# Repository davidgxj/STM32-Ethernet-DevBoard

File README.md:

STM32-Ethernet-DevBoard
=======================

STM32 F4 Ethernet Board

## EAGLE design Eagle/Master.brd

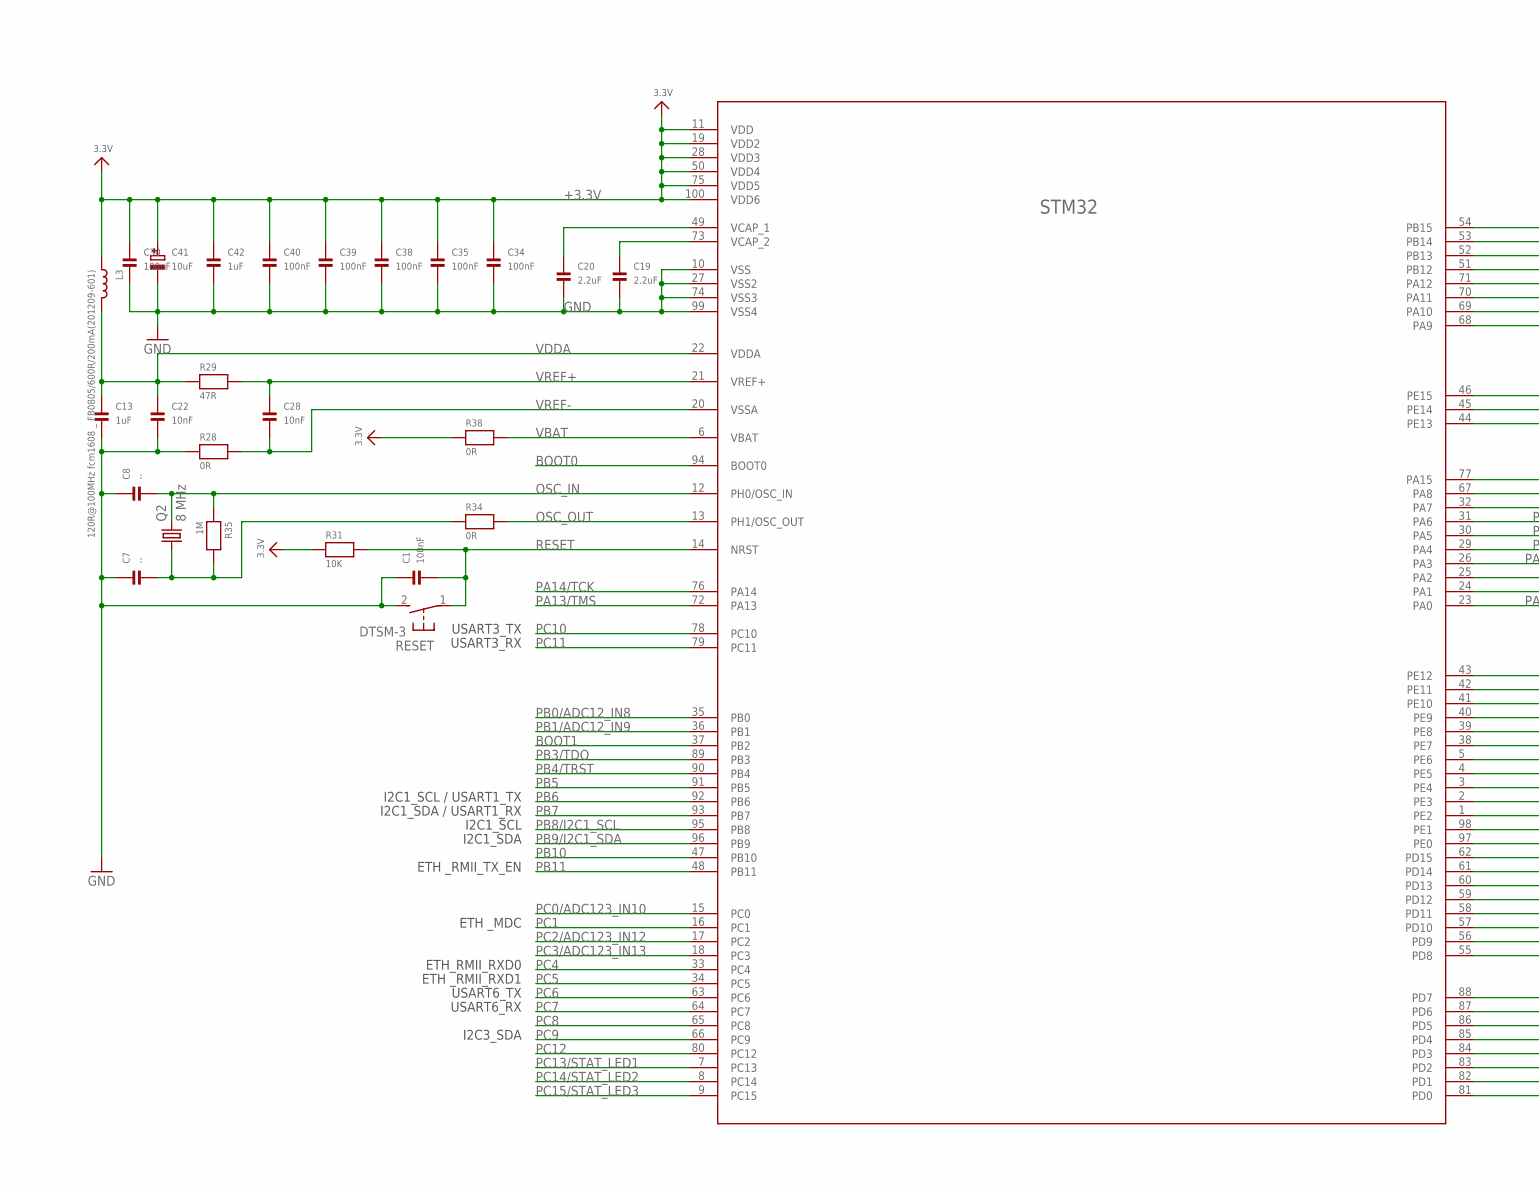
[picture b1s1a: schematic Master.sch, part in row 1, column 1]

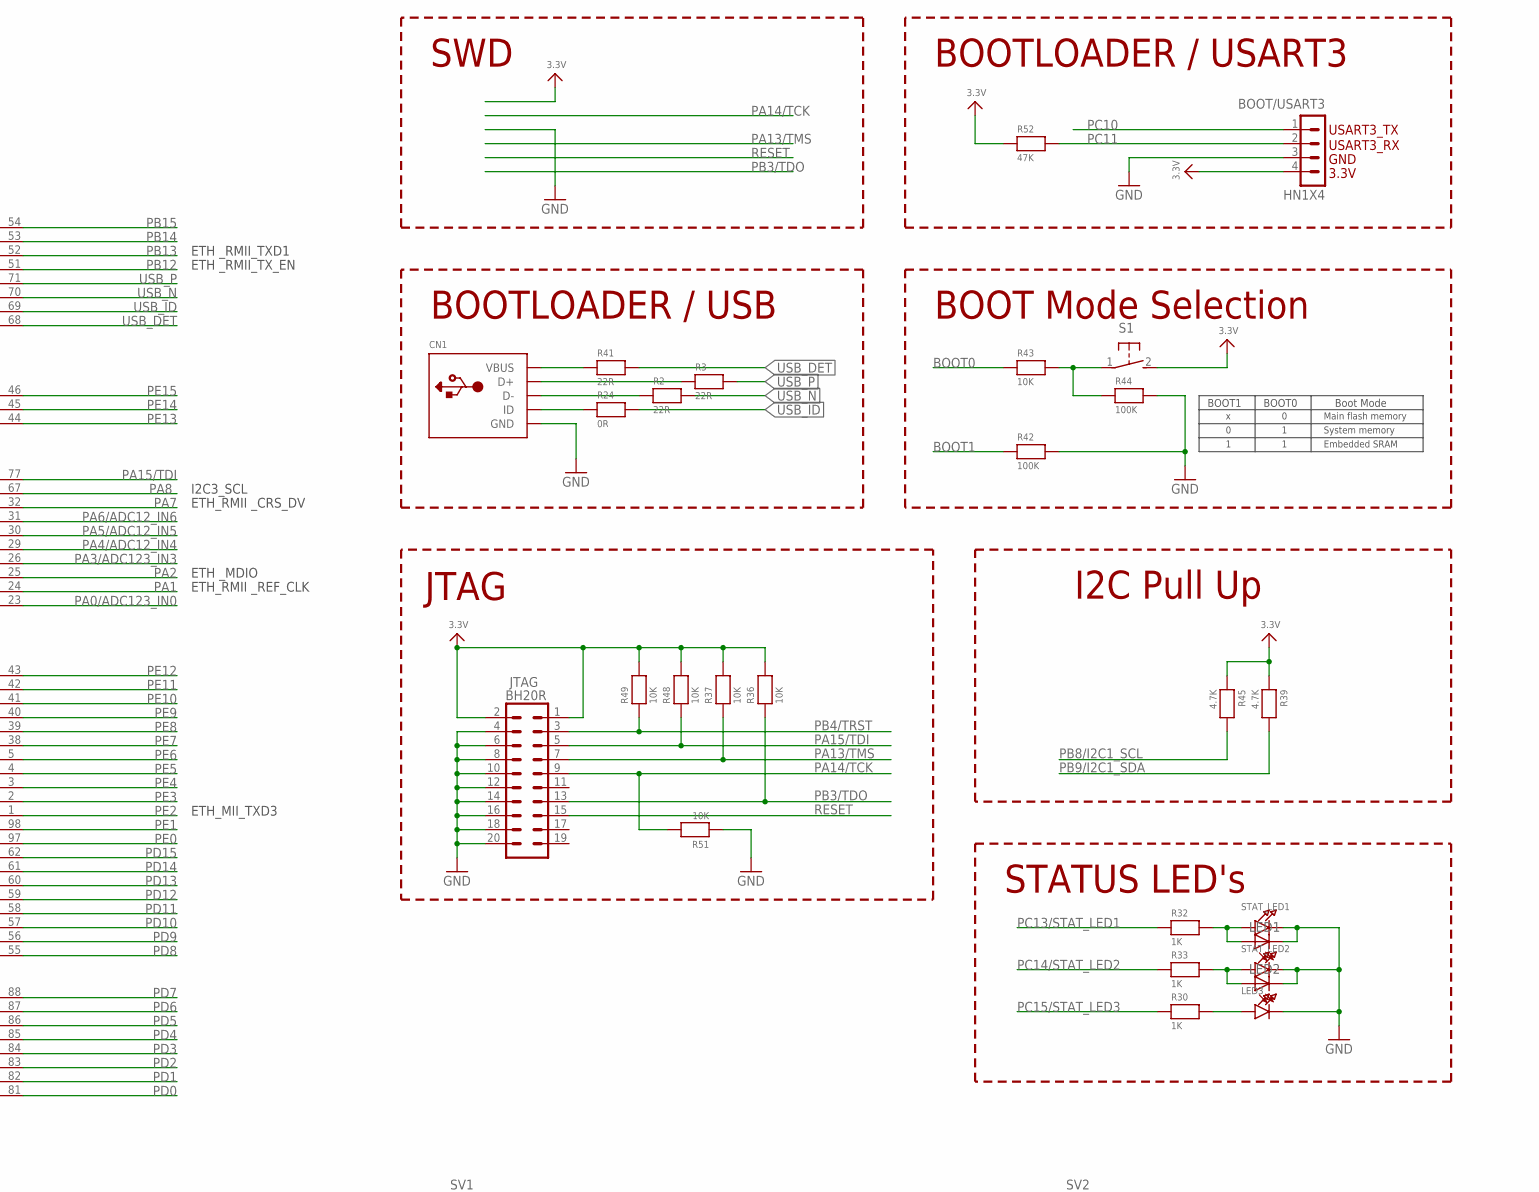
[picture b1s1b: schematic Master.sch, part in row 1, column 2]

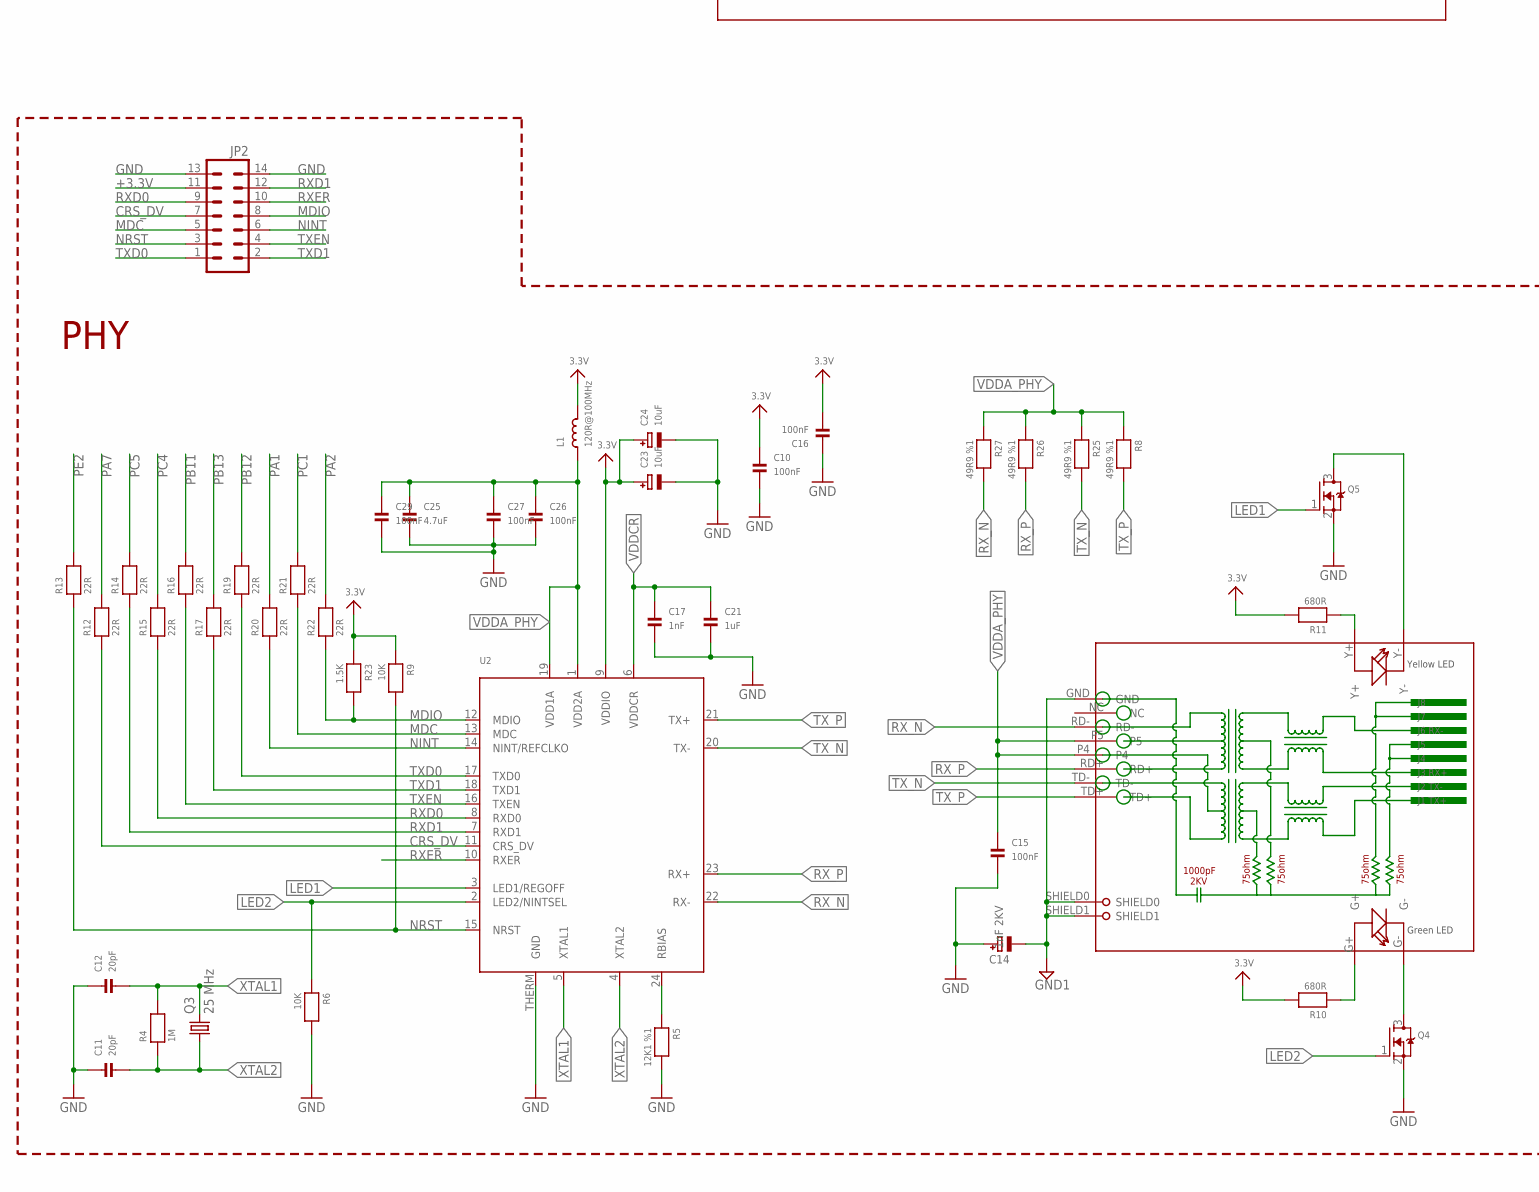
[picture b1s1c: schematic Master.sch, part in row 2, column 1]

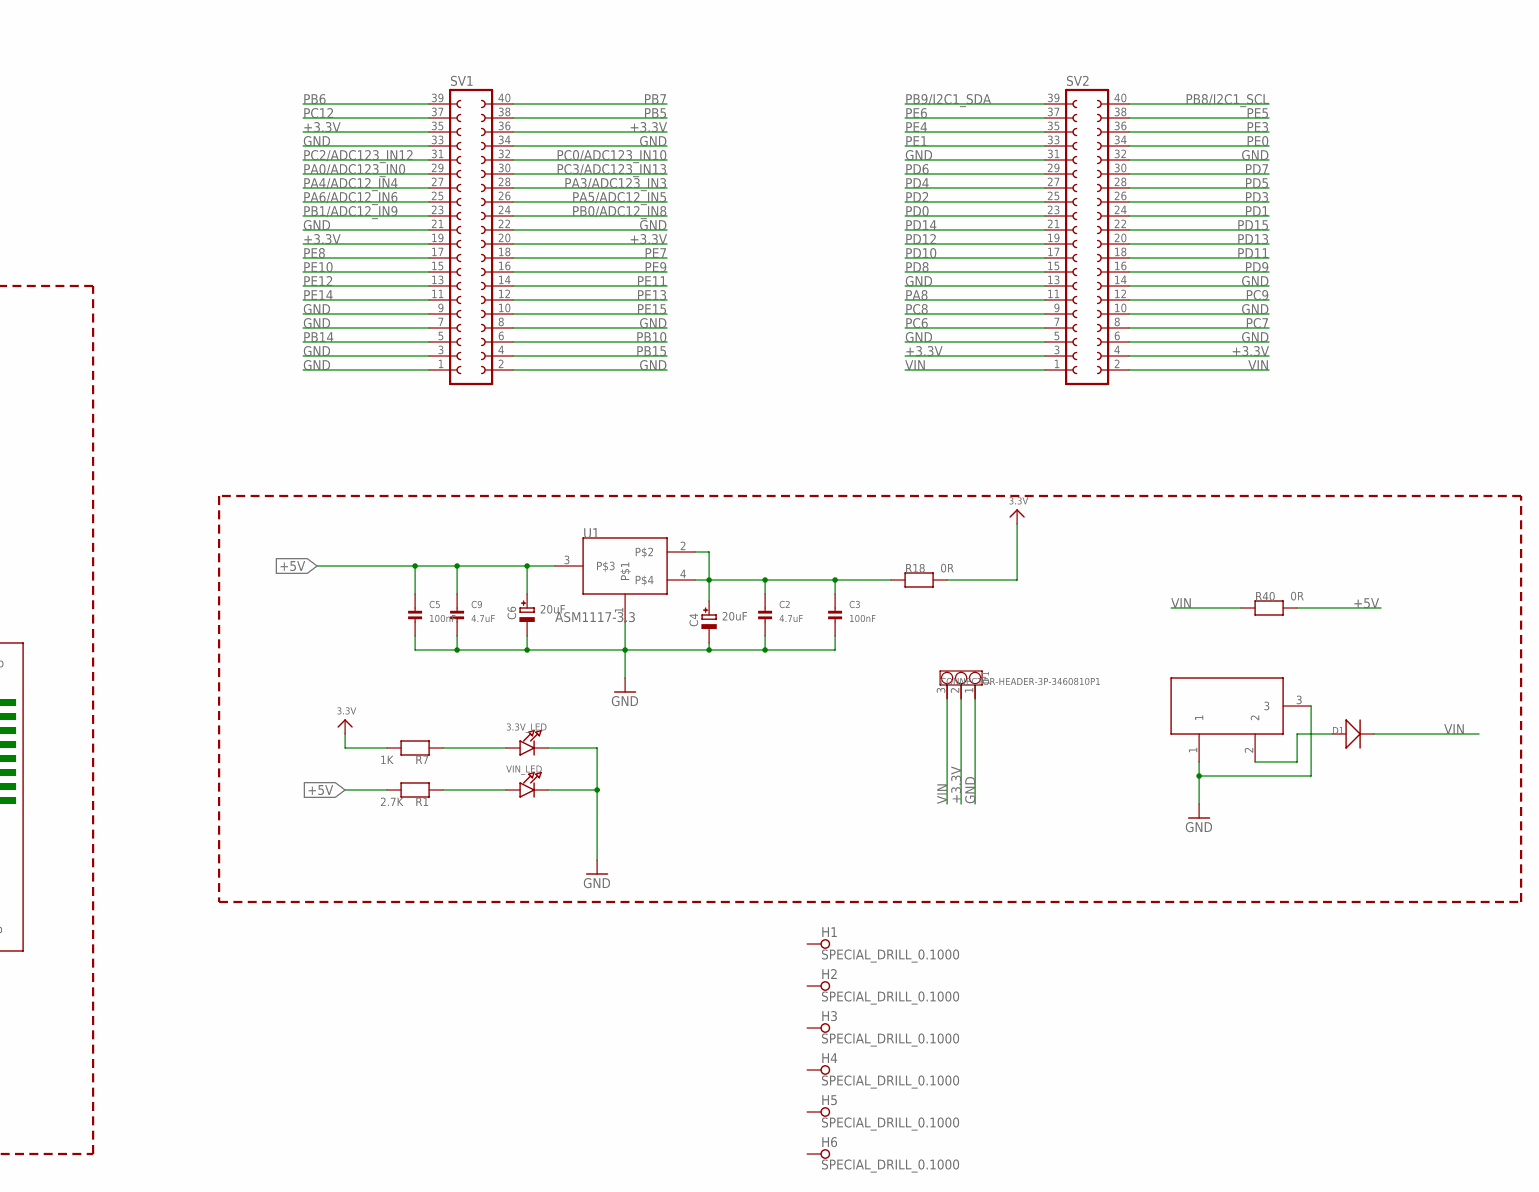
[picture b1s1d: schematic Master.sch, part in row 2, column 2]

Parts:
3.3V_LED: LED0805; CHIPLED_0805
BOOT/USART3: HN1X4
C1, C10, C16, C26, C27, C29, C30, C34, C35, C38, C39, C40: 100nF; _0603
C2, C9: 4.7uF; 0805
C3, C5: 100nF; 0805
C4, C6: 20uF; EIA3528-21/B-R
C7, C8: --; _0603
C11, C12: 20pF; _0603
C13, C21, C42: 1uF; _0805
C14: 1nF 2KV; EIA3528-21/B-R
C15: 100nF; _0805
C17: 1nF; _0603
C19, C20: 2.2uF; 1206
C22, C28: 10nF; _0603
C23, C24, C41: 10uF; EIA3528-21/B-R
C25: 4.7uF; _0805
CN1: USBMINIBLARGE; USB-MINIB_LARGER
D1: D-D1206; LL-34
H1, H2, H3, H4, H5, H6: SPECIAL_DRILL_0.1000; PAD_0.1000
JP1: CONNECTOR-HEADER-3P-3460810P1; 1X3P-2.54-2.54-11.6-3.0-BLACK-MALE
JP2: MA07-2
JTAG: BH20R
L1: 120R@100MHz; _0805
L3: 120R@100MHz fcm1608 _ FB0805/600R/200mA(201209-60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; _0805
LED1, LED2: LED5MM
LED3: LED0805; CHIPLED_0805
Q2: 8 MHz; HC49UP
Q3: 25 MHz; HC49UP
Q4, Q5: MOSFET-NWIDE; SOT23-WIDE
R1: 2.7K; _0603
R2, R3, R12, R13, R14, R15, R16, R17, R19, R20, R21, R22, R41: 22R; _0603
R4, R35: 1M; _0603
R5: 12K1 %1; _0603
R6, R9, R31, R36, R37, R43, R48, R49, R51: 10K; _0603
R7, R30, R32, R33: 1K; _0603
R8, R25, R26, R27: 49R9 %1; _0603
R10, R11: 680R; _0805
R18, R40: 0R; 0805
R23: 1.5K; _0603
R24, R28, R34, R38: 0R; _0603
R29: 47R; _0603
R39, R45: 4.7K; 1206
R42, R44: 100K; _0603
R52: 47K; _0603
RESET: DTSM-3
RJ1: HR911105A
S1: 31-XX; B3F-31XX
STAT_LED1, STAT_LED2: LED0805; CHIPLED_0805
STM32: STM32F407; 100LQFP
SV1, SV2: FE20-2
U1: ASM1117-3.3; SOT223
U2: LAN8720; QFN24_4MM
VIN_LED: LED0805; CHIPLED_0805
X1: DC21MMX; DC-21MM

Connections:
+3.3V: BOOT/USART3.4, C10.1, C16.2, C23.+, C24.+, C30.1, C34.1, C35.1, C38.1, C39.1, C40.1, C41.+, C42.1, JP1.2, JP2.11, JTAG.1, JTAG.2, L1.2, L3.1, R7.2, R9.1, R10.2, R11.2, R18.2, R23.1, R31.1, R36.2, R37.2, R38.1, R39.1, R45.1, R48.2, R49.2, R52.1, S1.2 (S), STM32.11 (VDD), STM32.19 (VDD2), STM32.28 (VDD3), STM32.50 (VDD4), STM32.75 (VDD5), STM32.100 (VDD6), SV1.19, SV1.20, SV1.35, SV1.36, SV2.3, SV2.4, U2.9 (VDDIO)
+5V: C5.1, C6.+, C9.1, R1.2, R40.2, U1.3
BOOT0: R43.1, STM32.94 (BOOT0)
BOOT1: R42.1, STM32.37 (PB2)
CRS_DV: JP2.7, R12.1, U2.11 (CRS_DV)
GND: 3.3V_LED.C, BOOT/USART3.3, C1.1, C2.2, C3.2, C4.-, C5.2, C6.-, C7.1, C8.1, C9.2, C10.2, C11.1, C12.1, C13.2, C14.+, C15.2, C16.1, C17.2, C19.2, C20.2, C21.2, C22.2, C23.-, C24.-, C25.2, C26.2, C27.2, C29.2, C30.2, C34.2, C35.2, C38.2, C39.2, C40.2, C41.-, C42.2, CN1.GND, JP1.1, JP2.13, JP2.14, JTAG.4, JTAG.6, JTAG.8, JTAG.10, JTAG.12, JTAG.14, JTAG.16, JTAG.18, JTAG.20, LED1.K (C), LED2.K (C), LED3.C, Q4.2 (S), Q5.2 (S), R5.2, R6.2, R28.1, R42.2, R44.2, R51.1, RESET.2, STAT_LED1.C, STAT_LED2.C, STM32.10 (VSS), STM32.27 (VSS2), STM32.74 (VSS3), STM32.99 (VSS4), SV1.1, SV1.2, SV1.3, SV1.7, SV1.8, SV1.9, SV1.21, SV1.22, SV1.33, SV1.34, SV2.5, SV2.6, SV2.10, SV2.13, SV2.14, SV2.31, SV2.32, U1.1, U2.THERM (GND), VIN_LED.C, X1.1, X1.3
GND1: C14.-, RJ1.GND, RJ1.SHIELD0, RJ1.SHIELD1
LED1: Q5.1 (G), U2.3 (LED1/REGOFF)
LED2: Q4.1 (G), R6.1, U2.2 (LED2/NINTSEL)
MDC: JP2.5, R21.1, U2.13 (MDC)
MDIO: JP2.8, R22.1, R23.2, U2.12 (MDIO)
unnamed: LED1.A, R32.2, STAT_LED1.A
unnamed: LED2.A, R33.2, STAT_LED2.A
unnamed: CN1.VBUS, R41.1
unnamed: LED3.A, R30.2
unnamed: D1.A (+), X1.2
unnamed: C2.1, C3.1, C4.+, R18.1, U1.2, U1.4
unnamed: 3.3V_LED.A, R7.1
unnamed: R43.2, R44.1, S1.1
unnamed: CN1.ID, R24.1
unnamed: R1.1, VIN_LED.A
unnamed: CN1.D+, R3.1
unnamed: R5.1, U2.24 (RBIAS)
unnamed: R10.1, RJ1.G+
unnamed: R11.1, RJ1.Y+
unnamed: Q4.3 (D), RJ1.G-
unnamed: Q5.3 (D), RJ1.Y-
unnamed: CN1.D-, R2.1
unnamed: C19.1, STM32.73 (VCAP_2)
unnamed: C20.1, STM32.49 (VCAP_1)
unnamed: C7.2, Q2.1, R34.1, R35.2
NINT: JP2.6, R20.1, U2.14 (NINT/REFCLKO)
NRST: JP2.3, R9.2, R13.1, U2.15 (NRST)
OSC_IN: C8.2, Q2.2, R35.1, STM32.12 (PH0/OSC_IN)
OSC_OUT: R34.2, STM32.13 (PH1/OSC_OUT)
PA0/ADC123_IN0: STM32.23 (PA0), SV1.29
PA1: R20.2, STM32.24 (PA1)
PA2: R22.2, STM32.25 (PA2)
PA3/ADC123_IN3: STM32.26 (PA3), SV1.28
PA4/ADC12_IN4: STM32.29 (PA4), SV1.27
PA5/ADC12_IN5: STM32.30 (PA5), SV1.26
PA6/ADC12_IN6: STM32.31 (PA6), SV1.25
PA7: R12.2, STM32.32 (PA7)
PA8: STM32.67 (PA8), SV2.11
PA13/TMS: JTAG.7, R37.1, STM32.72 (PA13)
PA14/TCK: JTAG.9, R51.2, STM32.76 (PA14)
PA15/TDI: JTAG.5, R48.1, STM32.77 (PA15)
PB0/ADC12_IN8: STM32.35 (PB0), SV1.24
PB1/ADC12_IN9: STM32.36 (PB1), SV1.23
PB3/TDO: JTAG.13, R36.1, STM32.89 (PB3)
PB4/TRST: JTAG.3, R49.1, STM32.90 (PB4)
PB5: STM32.91 (PB5), SV1.38
PB6: STM32.92 (PB6), SV1.39
PB7: STM32.93 (PB7), SV1.40
PB8/I2C1_SCL: R45.2, STM32.95 (PB8), SV2.40
PB9/I2C1_SDA: R39.2, STM32.96 (PB9), SV2.39
PB10: STM32.47 (PB10), SV1.6
PB11: R16.2, STM32.48 (PB11)
PB12: R19.2, STM32.51 (PB12)
PB13: R17.2, STM32.52 (PB13)
PB14: STM32.53 (PB14), SV1.5
PB15: STM32.54 (PB15), SV1.4
PC0/ADC123_IN10: STM32.15 (PC0), SV1.32
PC1: R21.2, STM32.16 (PC1)
PC2/ADC123_IN12: STM32.17 (PC2), SV1.31
PC3/ADC123_IN13: STM32.18 (PC3), SV1.30
PC4: R15.2, STM32.33 (PC4)
PC5: R14.2, STM32.34 (PC5)
PC6: STM32.63 (PC6), SV2.7
PC7: STM32.64 (PC7), SV2.8
PC8: STM32.65 (PC8), SV2.9
PC9: STM32.66 (PC9), SV2.12
PC10: BOOT/USART3.1, STM32.78 (PC10)
PC11: BOOT/USART3.2, R52.2, STM32.79 (PC11)
PC12: STM32.80 (PC12), SV1.37
PC13/STAT_LED1: R32.1, STM32.7 (PC13)
PC14/STAT_LED2: R33.1, STM32.8 (PC14)
PC15/STAT_LED3: R30.1, STM32.9 (PC15)
PD0: STM32.81 (PD0), SV2.23
PD1: STM32.82 (PD1), SV2.24
PD2: STM32.83 (PD2), SV2.25
PD3: STM32.84 (PD3), SV2.26
PD4: STM32.85 (PD4), SV2.27
PD5: STM32.86 (PD5), SV2.28
PD6: STM32.87 (PD6), SV2.29
PD7: STM32.88 (PD7), SV2.30
PD8: STM32.55 (PD8), SV2.15
PD9: STM32.56 (PD9), SV2.16
PD10: STM32.57 (PD10), SV2.17
PD11: STM32.58 (PD11), SV2.18
PD12: STM32.59 (PD12), SV2.19
PD13: STM32.60 (PD13), SV2.20
PD14: STM32.61 (PD14), SV2.21
PD15: STM32.62 (PD15), SV2.22
PE0: STM32.97 (PE0), SV2.34
PE1: STM32.98 (PE1), SV2.33
PE2: R13.2, STM32.1 (PE2)
PE3: STM32.2 (PE3), SV2.36
PE4: STM32.3 (PE4), SV2.35
PE5: STM32.4 (PE5), SV2.38
PE6: STM32.5 (PE6), SV2.37
PE7: STM32.38 (PE7), SV1.18
PE8: STM32.39 (PE8), SV1.17
PE9: STM32.40 (PE9), SV1.16
PE10: STM32.41 (PE10), SV1.15
PE11: STM32.42 (PE11), SV1.14
PE12: STM32.43 (PE12), SV1.13
PE13: STM32.44 (PE13), SV1.12
PE14: STM32.45 (PE14), SV1.11
PE15: STM32.46 (PE15), SV1.10
RESET: C1.2, JTAG.15, R31.2, RESET.1, STM32.14 (NRST)
RXD0: JP2.9, R15.1, U2.8 (RXD0)
RXD1: JP2.12, R14.1, U2.7 (RXD1)
RXER: JP2.10, U2.10 (RXER)
RX_N: R27.2, RJ1.RD-, U2.22 (RX-)
RX_P: R26.2, RJ1.RD+, U2.23 (RX+)
TXD0: JP2.1, R19.1, U2.17 (TXD0)
TXD1: JP2.2, R17.1, U2.18 (TXD1)
TXEN: JP2.4, R16.1, U2.16 (TXEN)
TX_N: R25.2, RJ1.TD-, U2.20 (TX-)
TX_P: R8.2, RJ1.TD+, U2.21 (TX+)
USB_DET: R41.2, STM32.68 (PA9)
USB_ID: R24.2, STM32.69 (PA10)
USB_N: R2.2, STM32.70 (PA11)
USB_P: R3.2, STM32.71 (PA12)
VBAT: R38.2, STM32.6 (VBAT)
VDDA: C13.1, C22.1, L3.2, R29.1, STM32.22 (VDDA)
VDDA_PHY: C15.1, C25.1, C26.1, C27.1, C29.1, L1.1, R8.1, R25.1, R26.1, R27.1, RJ1.P4, RJ1.P5, U2.1 (VDD2A), U2.19 (VDD1A)
VDDCR: C17.1, C21.1, U2.6 (VDDCR)
VIN: D1.C (-), JP1.3, R40.1, SV2.1, SV2.2
VREF+: C28.1, R29.2, STM32.21 (VREF+)
VREF-: C28.2, R28.2, STM32.20 (VSSA)
XTAL1: C12.2, Q3.2, R4.2, U2.5 (XTAL1)
XTAL2: C11.2, Q3.1, R4.1, U2.4 (XTAL2)

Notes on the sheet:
ETH_RMII _REF_CLK
ETH _MDIO
ETH_RMII _CRS_DV
ETH _RMII_TX_EN
ETH _RMII_TXD1
ETH _MDC
ETH_RMII_RXD0
ETH _RMII_RXD1
ETH_MII_TXD3
I2C Pull Up
BOOTLOADER / USB
SWD
BOOT Mode Selection
BOOT1
BOOT0
Boot Mode
Main flash memory
System memory
Embedded SRAM
STATUS LED's
I2C3_SCL
I2C1_SCL / USART1_TX
I2C1_SDA / USART1_RX
I2C1_SCL
I2C1_SDA
I2C3_SDA
PHY
USART3_TX
USART3_RX
GND
3.3V
BOOTLOADER / USART3
USART6_TX
USART6_RX
JTAG

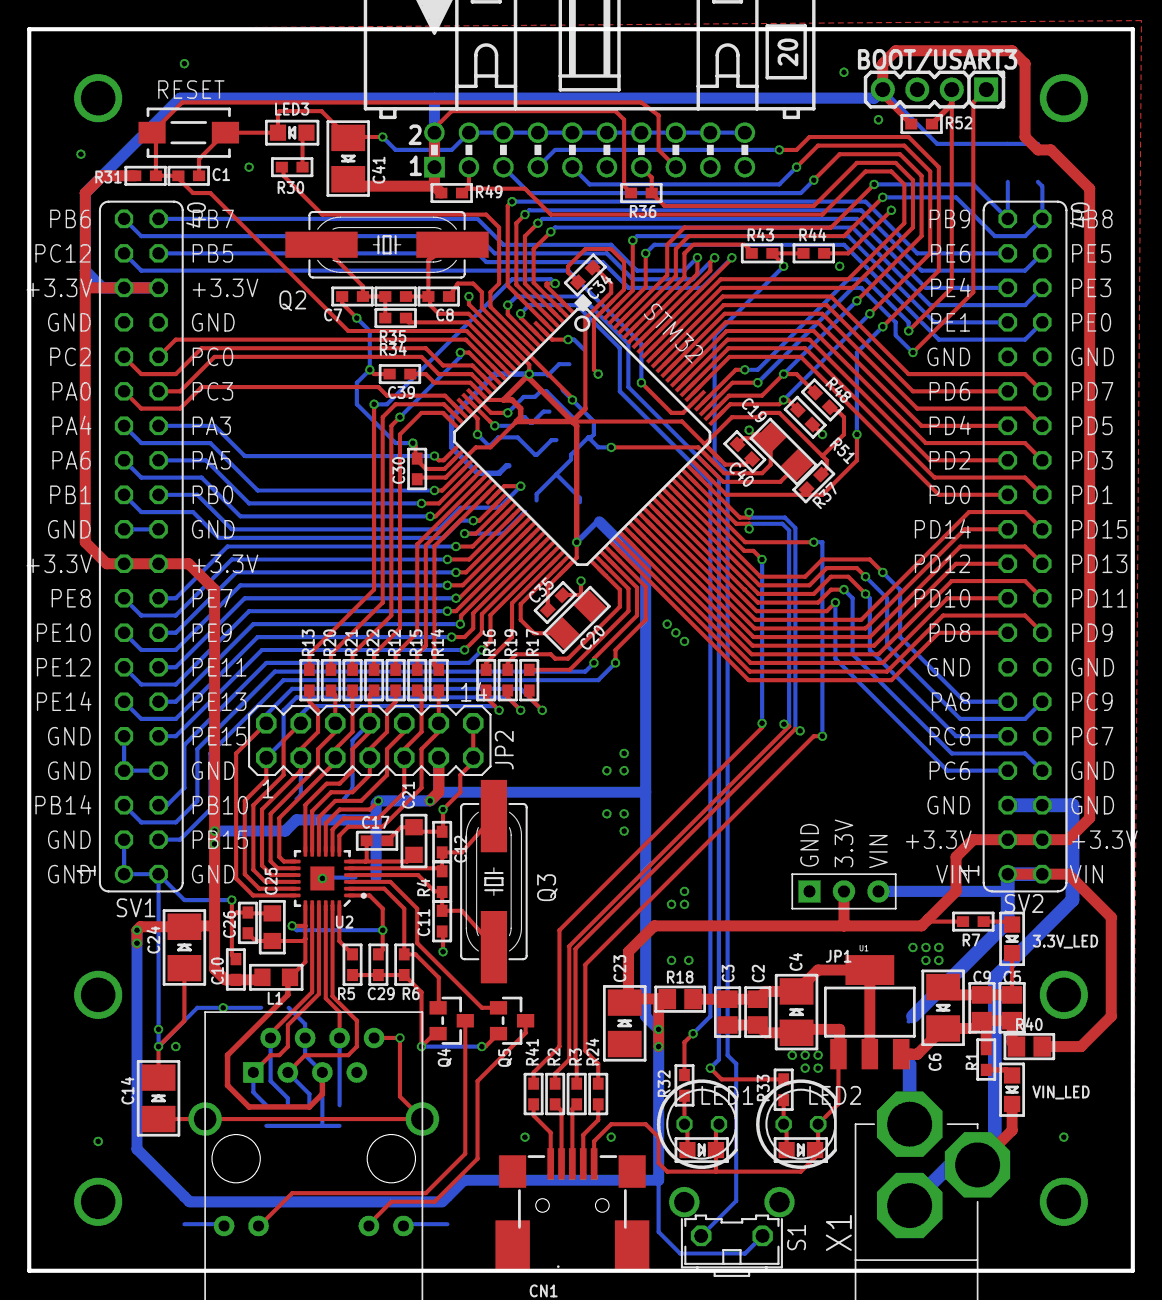
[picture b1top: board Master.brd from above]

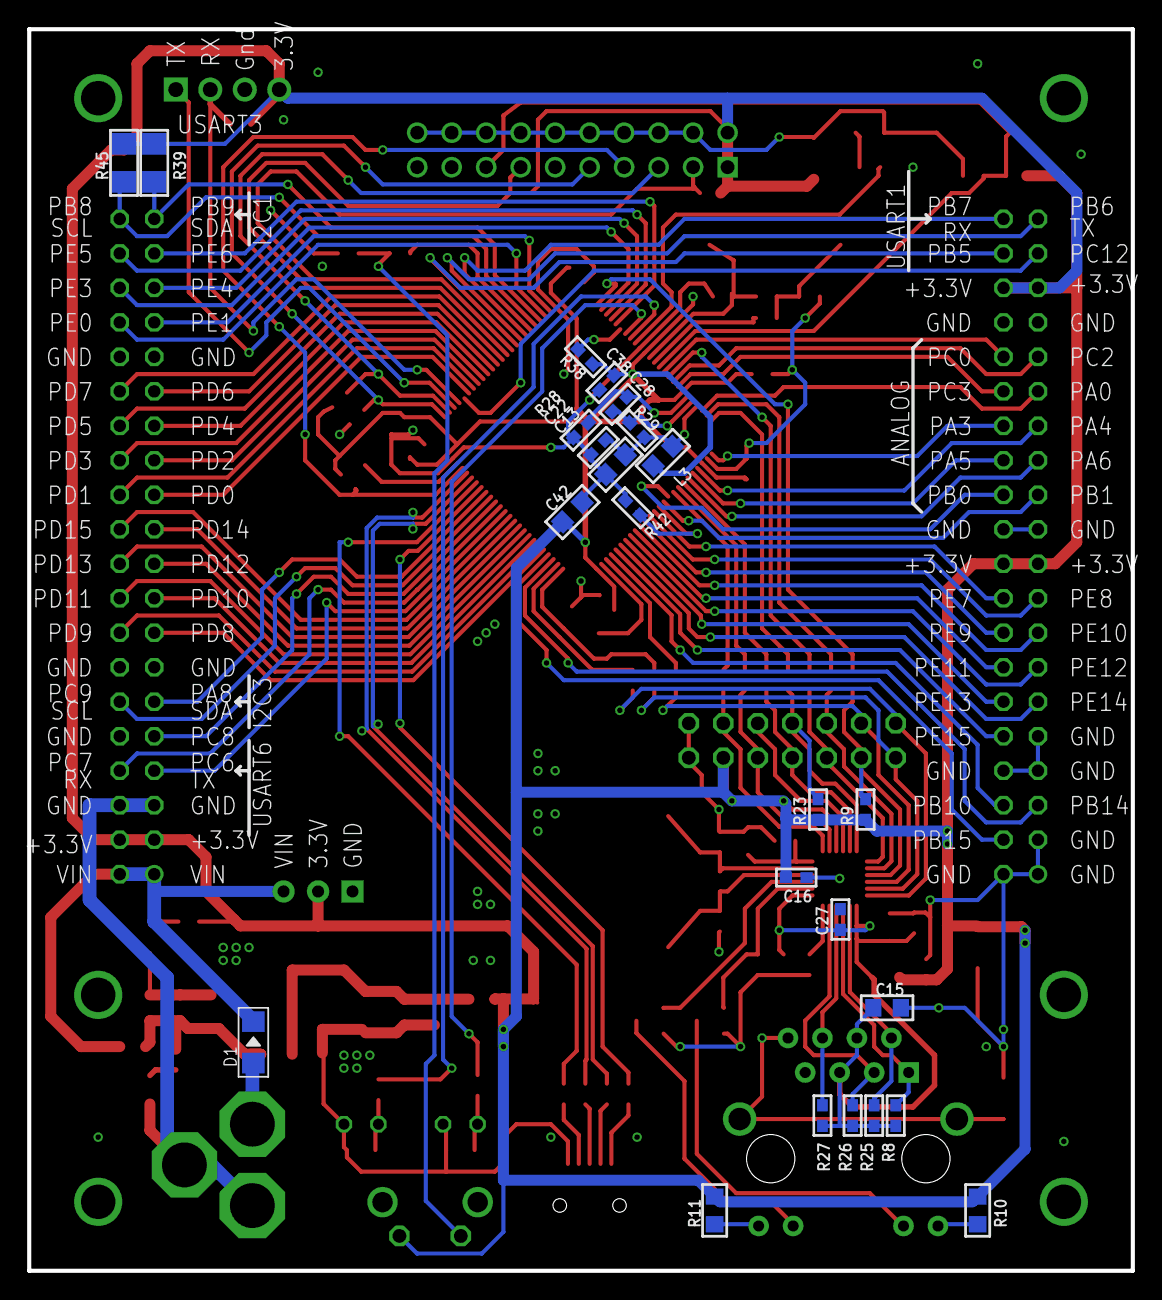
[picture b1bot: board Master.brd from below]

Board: 4 copper layers, 81.3 x 91.4 mm, 119 parts (24 on the bottom side), 134 nets.

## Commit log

2014-03-31 First Version.

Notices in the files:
parts and their libraries:
microbuilder: This work is placed in the public domain, and may be freely used for commercial and non-commercial work with the following conditions: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
